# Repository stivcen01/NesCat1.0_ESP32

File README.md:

# NesCat1.0_ESP32
Due to increased popularity of NesCat 0.5 project, I remastered old version of NESCAT 1.0 (NCAT) project (this is deprecated version).
This is experimental version and nothing is guaranteed.

SCHEMATIC:

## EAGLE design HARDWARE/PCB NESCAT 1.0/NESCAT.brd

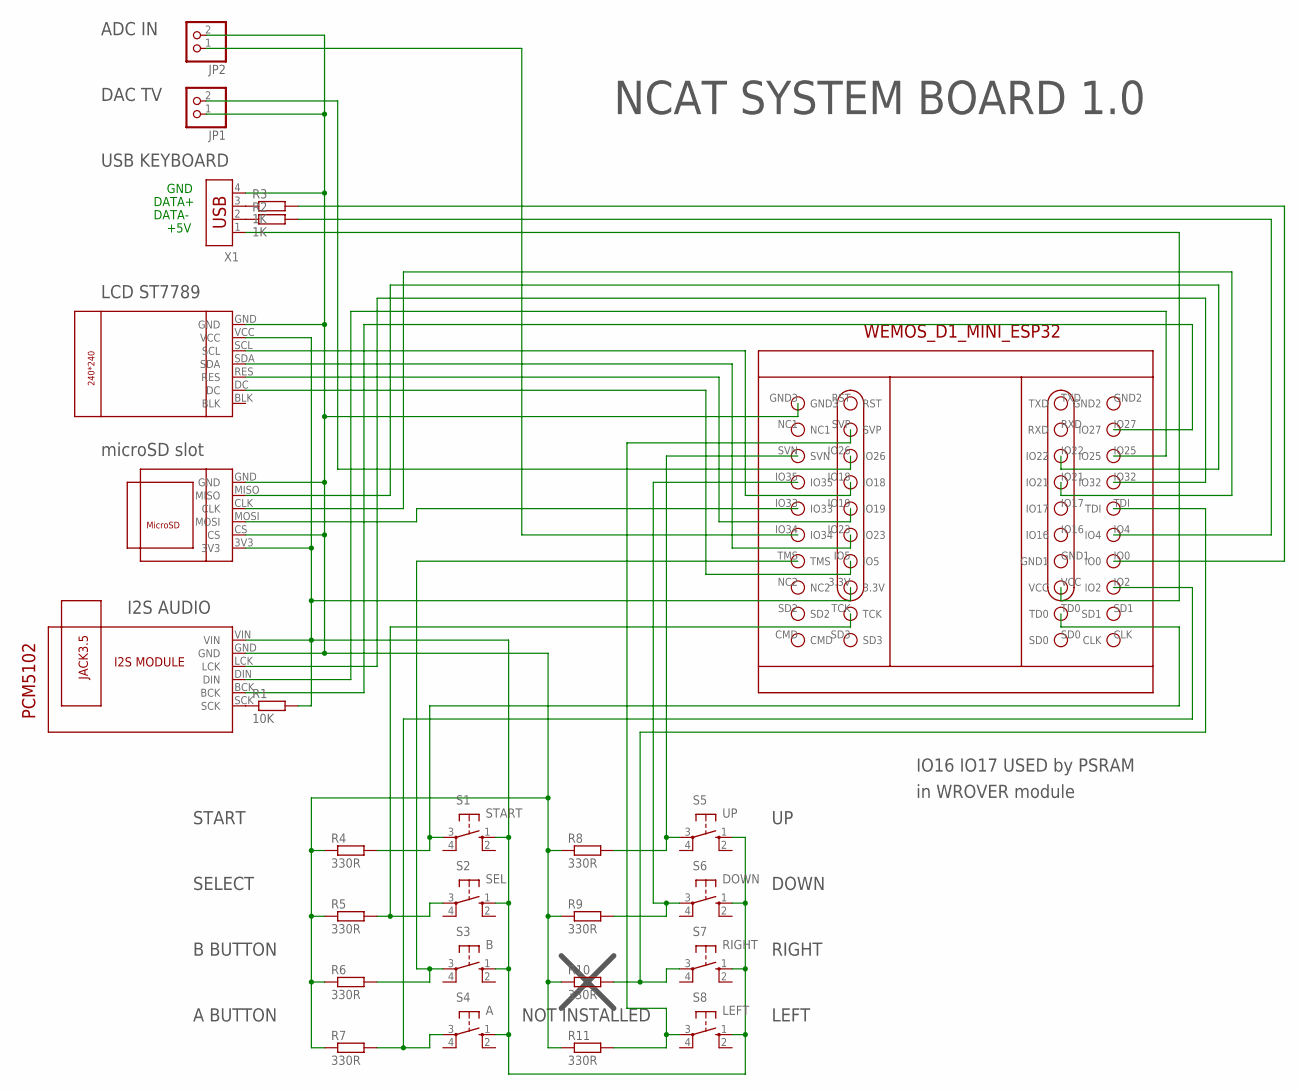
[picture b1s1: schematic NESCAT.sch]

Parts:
JP1, JP2: PINHD-1X2/90; 1X02/90
R1: 10K; R-0207/10H
R2, R3: 1K; R-0207/10H
R4, R5, R6, R7, R8, R9, R10, R11: 330R; R-0207/10H
S1: START; B3F-10XX
S2: SEL; B3F-10XX
S3: B; B3F-10XX
S4: A; B3F-10XX
S5: UP; B3F-10XX
S6: DOWN; B3F-10XX
S7: RIGHT; B3F-10XX
S8: LEFT; B3F-10XX
U$1: WEMOS_D1_MINI_ESP32
U$2: ST7789-1.3INCH
U$3: MICROSD-CARD-MODULE
U$4: I2S-MODULE-PCM5102A-LITE
X1: USB-787616; USB

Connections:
unnamed: U$1.IO32, U$4.LCK
unnamed: R1.1, U$4.SCK
unnamed: JP1.2, U$1.IO26
unnamed: R2.1, X1.2
unnamed: R3.1, X1.3
unnamed: U$1.VCC, X1.1
unnamed: R7.2, S4.3, U$1.IO2
unnamed: U$1.IO27, U$4.BCK
unnamed: R1.2, S1.1 (S), S2.1 (S), S3.1 (S), S4.1 (S), S5.1 (S), S6.1 (S), S7.1 (S), S8.1 (S), U$1.3.3V, U$2.VCC, U$3.3V3, U$4.VIN
unnamed: U$1.IO25, U$4.DIN
unnamed: U$1.IO18, U$2.SCL
unnamed: U$1.IO23, U$2.SDA
unnamed: U$1.IO19, U$2.RES
unnamed: R8.2, S5.3, U$1.SVN
unnamed: R5.2, S2.3, U$1.TCK
unnamed: R6.2, S3.3, U$1.TMS
unnamed: U$1.IO33, U$3.MOSI
unnamed: U$1.IO5, U$2.DC
unnamed: U$1.IO22, U$3.MISO
unnamed: U$1.IO21, U$3.CLK
unnamed: R9.2, S6.3, U$1.IO35
unnamed: R4.2, S1.3, U$1.TD0
unnamed: JP2.1, U$1.IO34
unnamed: R2.2, U$1.IO4
unnamed: R3.2, U$1.IO0
unnamed: R11.2, S8.3, U$1.SVP
unnamed: R10.2, S7.3, U$1.TDI
unnamed: JP1.1, JP2.2, R4.1, R5.1, R6.1, R7.1, R8.1, R9.1, R10.1, R11.1, U$1.GND3, U$2.GND, U$3.CS, U$3.GND, U$4.GND, X1.4

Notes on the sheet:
+5V
DATA-
DATA+
GND
ADC IN
DAC TV
USB KEYBOARD
LCD ST7789
microSD slot
I2S AUDIO
NOT INSTALLED
IO16 IO17 USED by PSRAM
in WROVER module
START
SELECT
A BUTTON
B BUTTON
DOWN
RIGHT
LEFT
NCAT SYSTEM BOARD 1.0

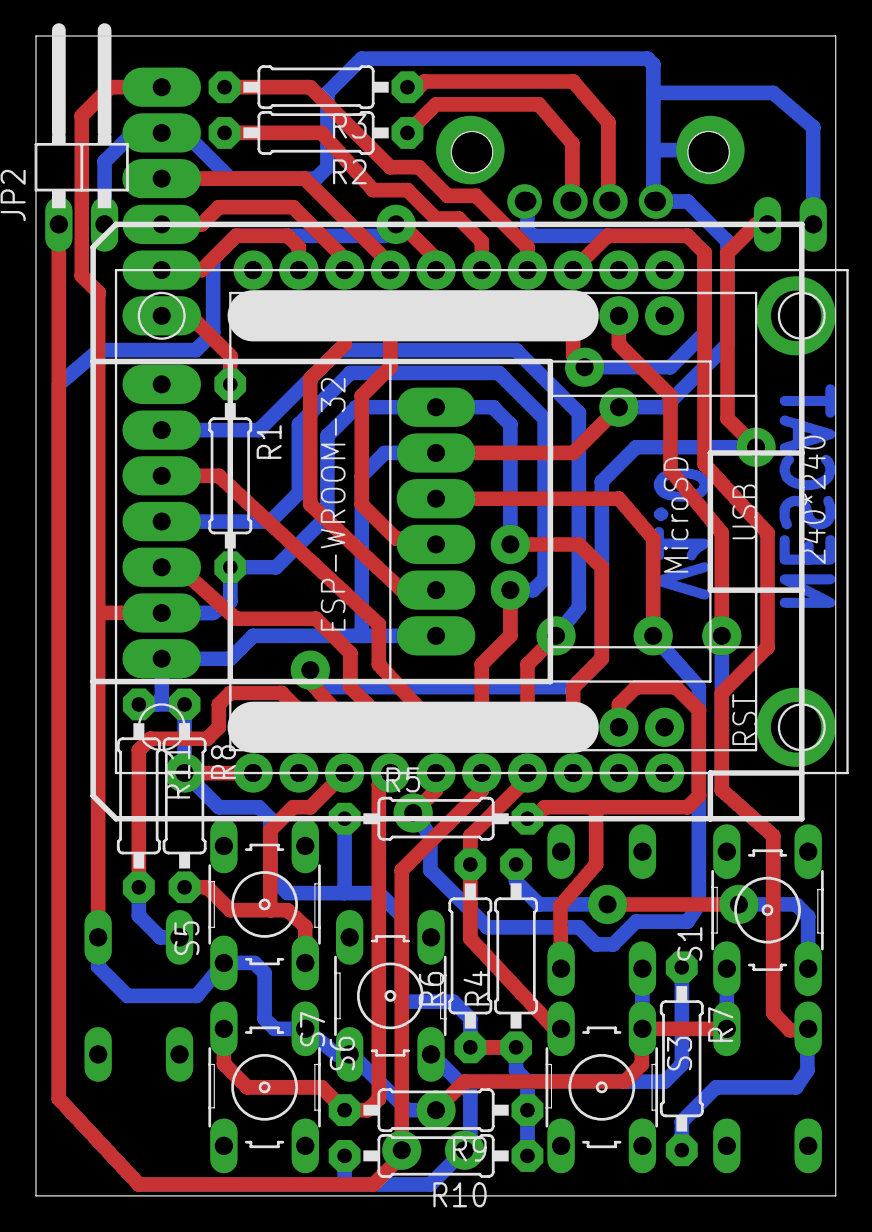
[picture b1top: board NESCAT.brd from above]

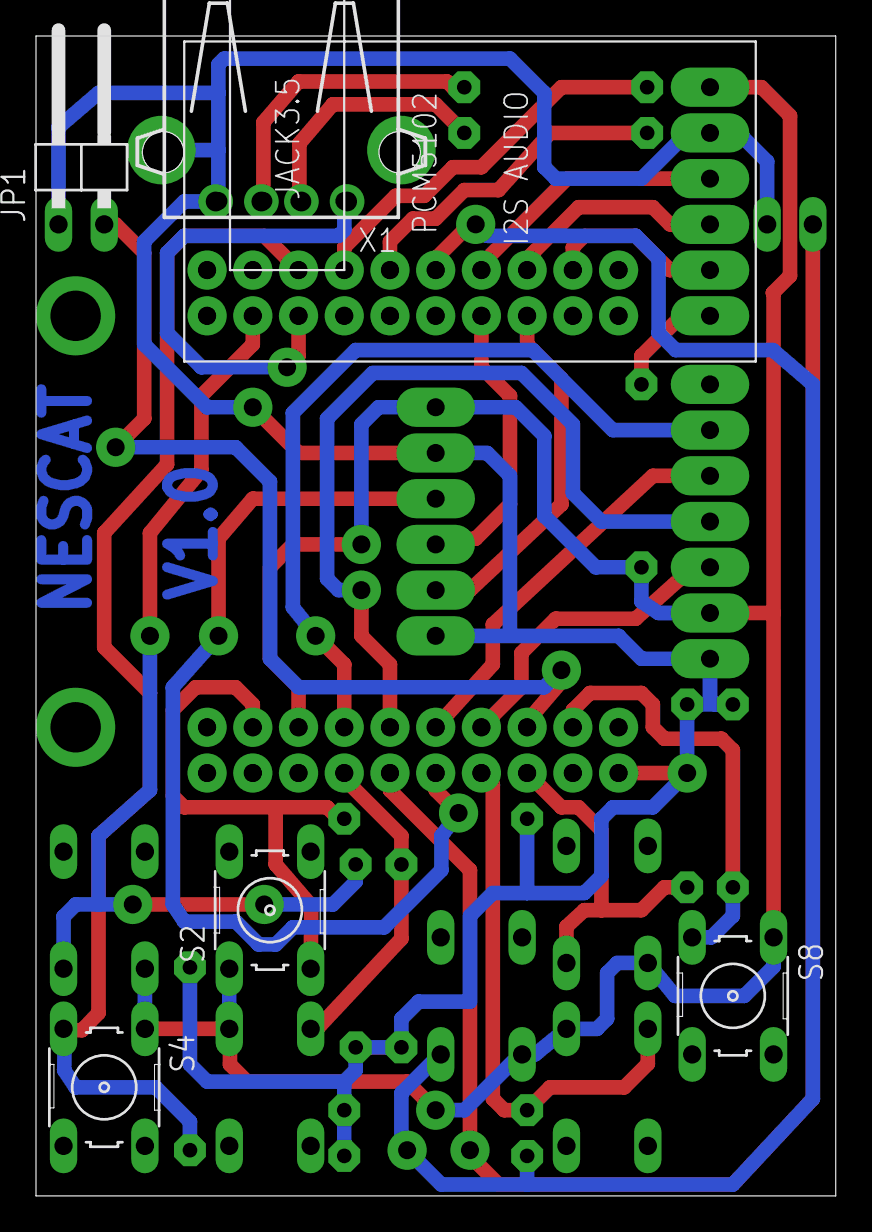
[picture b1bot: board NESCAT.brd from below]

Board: 2 copper layers, 44.4 x 64.4 mm, 26 parts (6 on the bottom side), 28 nets.

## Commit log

2022-01-24 MAIN
